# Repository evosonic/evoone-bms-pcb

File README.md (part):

# EvoOne BMS PCB (EVO2513 v0.6.0)

KiCad project for the EvoOne battery management board, EVO2513 revision 0.6.0.
Revision 0.6.0 is the 0.5.0 design (the boards in field test) with the W16
review changes below. The project, schematic and PCB files are named
`EVO2513`; the project libraries keep their `EVO2513-0_5_0` names.

The design was converted to KiCad from the Altium sources supplied by Lattech.
The raw import needed several fixes before the schematic and PCB agreed; see
[Fixes after import](#fixes-after-import).

## Board

| | |
|---|---|
| Outline | 110 × 69 mm |
| Layers | 8 copper (F.Cu, In1–In6.Cu, B.Cu) |
| Thickness | 1.598 mm finished (1.59 mm laminate + ENIG); stackup as the Altium fab drawing: three 0.25 mm cores, 2116 prepregs, 1 oz copper |
| Components | ~230 footprints |
| Tool | KiCad 10.0 |

## Schematic sheets

The schematic is hierarchical: the root sheet `EVO2513.kicad_sch` holds
one sheet symbol per sheet, and each sheet is its own file. Open it from
`EVO2513.kicad_pro`.

| Sheet | Function | Key parts |
|---|---|---|
| S01 External Connectors | Board connectors, mounting and test points | J1–J6, TP1–TP26 |
| S02 Input Protection | Over/under-voltage and reverse-voltage protection on the input | LTC4365, DMT4011LFG N-FETs |
| S03 BMS Input and Output Monitor | Input/output current sensing and power-path switching | LTC1960, DMP3018SFV P-FETs, 2512 shunts |
| S04 Charger Regulation | Charger switching stage | LTC1960, L1 4.7 µH |
| S05 Battery Management | Dual-battery selection and management | LTC1960 |
| S06 STEP-Up Step-Down Reg | Buck-boost output regulator | LM51772, L2 0.68 µH |
| S07 Load Switch and I-Sense | Output load switches and current-sense amplifiers | TPS22811 ×3, TLV9002 ×2 |
| S08 IO Expander | SPI I/O expander driving the rail enables and reading the faults | PCAL9714 |

The LTC1960 dual battery charger/selector is a single IC (U1) split across
sheets S03–S05.

Nets that cross sheets leave each sheet through a hierarchical label and a
pin on its sheet symbol, and the root sheet joins the pins with local
labels. There are no global labels; those nets are named from the root
(`/DCBMS`, `/POS1`, …). Labels between device sheets show the direction of
power or signal flow (e.g. DCFILTERED is an output of S02 and an input to
S03); links to the connector sheet, S01, stay passive. Labels used on only one sheet are local, and power
nets use power symbols.

## Connectors

| Ref | Part |
|---|---|
| J1 | Molex 1053101204, 2.5 mm pitch |
| J2 | Molex 1053101114, 14-way 2.5 mm pitch, vertical |
| J3 | Amphenol BergStak 10144517-043802LF, 40-pin 0.8 mm receptacle |
| J4 | Molex 1053102204, 2.5 mm pitch |
| J5, J6 | Molex 1053091102, 2-way 2.5 mm pitch |

The thermistor nets on J3 pins 24 and 28 are deliberately swapped from the
Altium design. The swap went in with `6ce5d68`, whose commit message doesn't
mention it. Firmware written for the earlier pinout must swap its BMSTEMP and
REGTEMP channels.

| J3 pin | Altium design | Now |
|---|---|---|
| 24 | BMSTEMP (TH1) | REGTEMP (TH2) |
| 28 | REGTEMP (TH2) | BMSTEMP (TH1) |

## Files

- `EVO2513.kicad_pro` — project
- `EVO2513.kicad_sch` — root schematic sheet; `S0x *.kicad_sch` — the
  eight sheets
- `EVO2513.kicad_pcb` — PCB layout
- `FIRMWARE_NOTES.md` — what the MCU firmware must know about this revision:
  SPI and expander set-up, the inverted DAQ enable, load-switch thresholds and
  current-monitor scaling
- `EVO2513-0_5_0-import-fps.pretty/` — project footprint library (footprints
  extracted by the Altium import), registered in `fp-lib-table`. Chip resistors
  and capacitors, the small diodes and the LEDs instead use KiCad's
  standard libraries (`Resistor_SMD`, `Capacitor_SMD`, `Diode_SMD`, `LED_SMD`,
  `Package_TO_SOT_SMD`, `Package_DFN_QFN`)
- `EVO2513-0_5_0-lattech.kicad_sym` — project symbol library (nickname
  `Lattech Systems`): the Lattech symbols used by the board, extracted from
  the schematics, plus the PCAL9714 added for the W16 changes. It is not the complete Lattech library, which was not supplied.
  Resistors and capacitors use KiCad's standard `Device:R`, `Device:C` and
  `Device:C_Polarized` symbols, with value, footprint and part number in the
  symbol fields, so a value change needs no new symbol
- `EVO2513-0_5_0-altium-import.kicad_sym` — the 4 power symbols created by the
  Altium import. Both symbol libraries are registered in `sym-lib-table`.

## Design changes (W16 review)

Part and value changes from the W16 schematic review. None changes a
connection or the board copper.

| Ref | Was | Now | Why |
|---|---|---|---|
| Q1, Q3 | DMT4011LFG 40 V | DMT6007LFGQ-7 60 V | Margin against D1's clamp voltage |
| D1 | 1.5SMB27CA | 1.0SMBJ26CA (Diotec) | Stand-off above the 24 V supply; 42.1 V clamp |
| L1 | 4.7 µH SRP1265A-4R7M | 10 µH SRP1265A-100M | LTC1960's 10 µH minimum |
| C10 | 100 nF 16 V | 100 nF 50 V CC0402KPX7R9BB104 | Sits on VPLUS at ~23 V |
| R54 | 1 kΩ | 768 Ω RC0402FR-07768RL | SBC load-switch current limit (R22, R53, R71 stay 1 kΩ) |
| C16 | 220 nF 50 V C0G 0805 | 220 nF 50 V X7R CC0805KFX7R9BB224 | No 220 nF C0G 0805 exists |
| C39 | 470 pF | 1 nF | SW2 snubber, boost-mode ringing |
| C3, C11, C12 | 35 V | 50 V | DCFILTERED / DCBMS at 26.3 V |
| C44, C45, C48–C50, C54 | 16 V | 50 V | +12 V and the switched outputs |
| R1 | 620K (description 619K) | 619K | Value and description now agree |
| C2 | 100 µF (part number `35SVPF82M`) | 82 µF `35SVPF82M` | Matches the ordered part |
| C46, C47, C51 | 4.7 nF 50 V X7R 0402 | 1.8 nF 50 V X7R 0402 `CC0402KRX7R9BB182` | TPS22811 DVDT caps (U6, U7, U9): shorter output ramp, as ordered for C47; the loads have little capacitance |
| R24–R27 | 10 Ω | 0 Ω | Pack comms pass straight through; protection moves to the MCU board |
| D9, D10 | DT1240V3-04LP fitted | DNP | Go with R24–R27: wrong clamp level for 3.3 V, and the protected MCU is on another board |
| R14 | 0.01 Ω | 0.012 Ω Yageo `PA2512FKE7W0R012E` | Adapter limit 8.33 A, below the 9.2 A supply, so charging throttles before the supply trips |
| R36 | 61.9K fitted | DNP | VIN-FB goes to ground through R37, as required when PCM is unused |
| R59, R61, R76 / R60, R62, R77 | 1M / 130K | **390K / 51K** | TPS22811 PGTH dividers: 10.38 V threshold, string current 23.5 µA at threshold to meet TI's 20× PGTH leakage rule, so pin leakage can't push it near the rail |
| R67, R68, R81 | 2.2K | **4.7K** | PG LED (LED2–LED4) resistors from +3V3MCU: about half the current, ≈0.25 mA each instead of ≈0.55 mA, which saves ≈0.9 mA on battery with all three rails up. 4.7K is already on the BOM (R10) |
| R90–R92, R101 | 1M | 1.07M | OVLO trip 14.0 V, so a tripped switch recovers on the 12.03 V rail; R101 shares the BOM line |
| U6 EN/UVLO | ENDAQ from P0_0, R49 100K pull-down | R108 **619K** / R49 **75K** UVLO divider, Q24 shutdown FET with R109 **1.07M** / R110 **390K** gate bias; net `nENDAQ`, active low | DAQ 11 V undervoltage lockout (W16 handoff §4.4) |
| R41, R45 | 2.2R 1% 1206, 1/4 W | 2.2R 1% **1210**, 1/2 W (any standard thick film) | Snubber resistors. R41 (SW1) dissipates 0.31 W at 24 V and 0.38 W at the 26.3 V OV trip, 75% of 1/2 W: fine up to about 90 °C local ambient. R45 (SW2) 0.167 W, 33%. Power is set by C·V²·f, not the load, so it is continuous at 1.157 MHz; power-save mode lowers it at light load. Same length as 1206; the pads are 0.45 mm wider each side |
| Q4, Q5, Q12–Q15 | DMP3018SFV, PowerDI3333-8 (Type UX), imported Altium land | **DMP3007SCG-13** (Diodes, V-DFN3333-8 Type B, 6.8 mΩ max at −10 V), `Diodes_PowerDI3333-8`, copied from KiCad's standard `Package_SON` library into the project library so it can carry the source-drain keepout | PowerPath/battery FET thermal margin (W16 handoff). KiCad has no Type B footprint; the PowerDI3333-8 one matches Diodes' Type B suggested land except 0.1 mm more toe on each pad row, and adds segmented paste on the drain. Its drain is one pad, 5, so the project symbol `DMP3007SCG V-DFN3333-8` numbers D pins 5–8 and EP_D all 5. VGSS ±25 V as before. Diodes' datasheet (DS38990 rev 3-2) is still marked Advance Information |
| Q18 | CSD17304Q3 | unchanged (kept) | The W16 handoff suggested a lower-RDS(on) 30 V part for the 1.83 W boost-mode loss. Kept: it works and 15 units are in field test. Its thermal margin depends on copper: 46 °C/W on 1 in² against 158 °C/W on a minimum pad, so give it the full copper area in layout |
| R16 | 0.005R 2512 (`CRE2512-FZ-R005E-3`) | **0.003R** Bourns `CRE2512-FZ-R003E-3` | The LTC1960 latching breaker (90–115 mV for 15 ms) moves from 18–23 A to 30–38 A. 12 V peak load is about 7.5 A SBC (90 W) + 2.5 A J3 + DAQ, over the handoff's ~11 A threshold, and QE29 packs at ~21 A would sit at 105 mV, inside the trip window. Dissipation at 21 A drops from 2.2 W to 1.3 W. R16 feeds only the breaker comparator (SCP/SCN) |
| R53, R71 | 1K | unchanged | DAQ and EXT current limits (6595/R = 6.6 A, up to 7.1 A) sit above J6/J5's single 6.5 A contact. Left at 1K: DAQ's final load isn't known (stand-in device today) and EXT is unused. A note on S07 says to raise them to 1.2K or more once the loads are known |
| D4 | Pins named as a series pair | Pins named for the fitted common-anode BAT54A | Drawing and wiring were already right |

Connection options on U5 (LM51772), as 0R 0402 links so either build can be
fitted (lower right of S06):
nRST stays on DCBMS in both BIAS builds.

| Pin | Fitted | DNP (alternative) |
|---|---|---|
| MODE (7) | R86 to GND: power-save mode (W16 review) | R87 back to VCC2: forced PWM, as built before |
| ILIMCOMP/ISET (16) | R116 13K and C55 100 pF to GND: average current limit and current monitor enabled | R103 to VCC2: current limit disabled, as built before |
| FB/SEL_intFB (14) | R117 to VCC2: internal feedback divider, output voltage set over I2C | R46 62K / R47 5.62K external divider, as built before |
| BIAS (40) | R89 to +12V (U5's own output): the LM51772 datasheet's standard configuration (§7.3.5). VSMART runs the VCC2 regulator from the lower of VIN and BIAS once both exceed the switch-over threshold, so on the 24 V supply it drops from 12 V instead of 24 V; at start-up or with +12V shorted it falls back to VIN | R88 to DCBMS, as built on the field units |

U5 is configured over I2C by default, not by its CFG resistors (parts right
of the MODE/BIAS links on S06):

| Ref | Part | Function in the I2C build (default) |
|---|---|---|
| R38 | 0R, CFG1 (ADDR/SLOPE, pin 9) to GND | Selects I2C at address 0x6A. 6.49K instead selects resistor configuration with slope compensation 1.0 |
| R104 | 0R, SDA/CFG3 (pin 5) to J3.34 `MCU_ENDAQ` | SDA to the MCU |
| R105 | 0R, SCL/CFG4 (pin 6) to J3.36 `MCU_ENEXT` | SCL to the MCU |
| R106, R107 | 10K to +3V3MCU | SDA and SCL pull-ups (pins rated to 5.8 V). 10K keeps edges slow for EMC and limits the bus to 100 kHz standard mode |
| R30, R29 | 5.1K and 1.87K to GND, **DNP** | CFG3/CFG4 for the resistor build; fitted, they would load the bus |

To return to the resistor build, remove R104–R107, change R38 to 6.49K and fit
R29 and R30. J3.34 and J3.36 are also the direct-enable fallback through R97
and R98 (S08), so R97 and R98 stay unfitted while the I2C build is fitted. The
MCU pins on J3.34/J3.36 must support I2C.

U5 starts from its register defaults, not the resistor
settings, so firmware must write them before raising REGEN. They are latched
for as long as DCBMS is up, since nRST is tied to DCBMS. Defaults that differ
from the resistor build:
- slope compensation is 0.875 (R38 selects 1.0)
- VCC1, DRSS, hiccup mode and the current-limit options come from registers
  instead of R30 and R29
- the internal DAC becomes the current-limit reference (`ILIM_THRESHOLD`);
  ILIMCOMP/ISET now has R116 13K and C55 100 pF to GND, so the average
  current limit is active: set `ILIM_THRESHOLD` to the intended limit
- R117 selects the internal feedback divider (R46/R47 DNP), so the +12V
  output voltage comes from U5's registers, not a resistor divider
- constant dead time (`EN_CONST_TDEAD`) defaults off; R30 (CFG3 setting 7)
  turns it on

Overvoltage lockout on the load switches U6, U7 and U9 (TPS22811, S07): a
1.07 MΩ 1% resistor (R90, R91, R92) from +12V to nEN/OVLO (pin 2), with the
existing 100K 1% pull-downs R51, R52 and R70. Each switch turns off above
14.0 V (13.40–14.69 V over the ±2% pin threshold, 1% resistors and ±0.1 µA pin
leakage) and turns back on below 12.75 V (12.23–13.41 V), so a tripped switch
always recovers on U5's 12.03 V output. (1 MΩ gave 13.2 V, recovering at
11.50–12.60 V, which might not.) To revert, leave R90–R92 unfitted.
The power-good dividers on PGTH are R59, R61 and R76 (390K) over R60, R62 and
R77 (51K): PG rises at 10.38 V (9.62–11.17 V worst case) and falls at 9.43 V
(8.71–10.22 V). They were 1M over 130K, but the ±1 µA PGTH leakage across 1M
could put the threshold at 11.84 V, within 0.2 V of the rail. TI sizes the
string for at least 20× the PGTH leakage (20 µA); 390K/51K carries 23.5 µA at
the threshold and 27 µA at 12 V, and only while the switch is on, because the
dividers hang off the switch outputs. 51K is already on the BOM.
Undervoltage lockout on the DAQ switch U6 only: R108 619K from +12V over R49
75K on EN/UVLO (pin 1) turns U6 on at 11.10 V (10.63–11.91 V, including
1% resistors, ±0.1 µA pin and 0.5 µA FET leakage) and off at 10.09 V
(9.69–10.89 V). TI asks for a pull-up of at least 350 kΩ on supplies above
5 V. 1M/120K would keep the 11.2 V point, but leakage across 1M puts the
worst-case turn-on at 12.24 V, above the rail; 619K and 75K are already on
the BOM and keep it under 12 V. The
TPS22811's fixed hysteresis makes the turn-off point about 9% below turn-on,
so 11 V has to be the turn-on point. Because the divider now holds EN/UVLO,
the enable goes through Q24 (BSS138) from EN/UVLO to GND, and the expander net
is `nENDAQ`, active low: high or floating (POR, expander in reset or
unpowered) turns Q24 on and puts U6 in shutdown; low releases EN/UVLO to the
divider. R109 1.07M / R110 390K bias the gate from +12V to 3.21 V (2.83 V at
10.6 V, 4.0 V worst case at the 14.7 V OVLO limit), so the channel stays off
when the MCU board is unpowered, and the gate stays under 5 V. The divider
draws 8.2 µA from +12V (it was 94 µA with 100K/27K), and both values are
shared with other BOM lines. The gate's source impedance is 286K, so P0_1 can
stay push-pull: driven high to 3.3 V it still holds Q24 on and sinks at most
2.4 µA, and the R97 fallback can drive it from a 3.3 V MCU pin. SBC and EXT have no
UVLO. A note on S07 marks the DAQ circuit as deliberate.

If the UVLO causes trouble, R115 (0R, DNP) bypasses it. Fit R115 and remove
Q24, R108 and R109: `nENDAQ` then drives EN/UVLO directly, as ENSBC and
ENEXT drive U7 and U9, so P0_1 (or the R97 fallback) becomes active high and
DAQ has no undervoltage lockout. R110 390K in parallel with R49 75K (62.9K) is
the pull-down that holds U6 off while the expander is in reset or unpowered.
Leaving R108 or R109 fitted with R115 would put a +12V divider on EN/UVLO, so
remove both.

Rail enables and faults through a PCAL9714 SPI I/O expander (U11, new sheet
S08). It shares CLOCK/MOSI/MISO with U1 (LTC1960) and has its own chip
select, nCSIO, on J3.32, the pin that was ENSBC. Address 40h (ADDR to GND);
INT has a pull-up but isn't routed off the board. Both supplies are
+3V3MCU. RESET is held low by R100 (100K) and pulled to +3V3MCU by Q23
(BSS138, the same FET as Q20-Q22) whenever +12V is up: R99 100K /
R101 1.07M put about 11 V on its gate. With the 12 V rail off the expander is
in reset with every port an input, and RESET can never rise above
+3V3MCU, so nothing back-powers the expander. The switch point depends on
Q23's gate threshold (roughly 3.5-4 V on +12V with a BSS138) and has no hysteresis, so
firmware should wait for +12V before configuring the expander.

Q20–Q23 are onsemi BSS138 (SOT-23) in place of the DMN65D8LFB-7
(DFN1006, 1.0 × 0.6 mm). Use the plain BSS138 or another part without a
gate protection zener: the gates sit on 100K pull-ups (R63, R65, R78) and
the R99/R101 divider, and ESD-protected parts such as the 2N7002K or
BSS138BK leak up to about 10 µA, which would pull the PG high level down
by about 1 V. BSS138: IGSS 100 nA, IDSS 0.5 µA, VGS(th) 0.8–1.5 V.

| Port | Net | Function |
|---|---|---|
| P0_0 (out) | ENSBC | U7 enable |
| P0_1 (out) | nENDAQ | U6 enable through Q24, **active low** |
| P0_2 (out) | ENEXT | U9 enable |
| P0_4–P0_6 (in) | PGDAQ, PGSBC, PGEXT | U6, U7, U9 power good (also still drive the LEDs) |
| P0_7 (in) | nFLT | U5 nFLT/nINT, which was unconnected |
| P0_3, P1_0–P1_5 | — | spare, not connected |

REGEN (U5 enable, J3.12) stays separate: it is still driven straight from
J3 and doesn't pass through the expander.

J3 pins 34 and 36 are now `MCU_ENDAQ` and `MCU_ENEXT`. Each reaches its
enable only through a DNP 0R link (R97, R98), and J3.32
`nCSIO` has R95 (fitted) to the expander CS and R96 (DNP) to ENSBC. To go
back to driving an enable straight from J3, fit its link and leave that
expander port an input. The expander powers up with every port an input
and pulls off, so the pull-downs (R50, R69) and Q24's gate bias keep the
rails off until firmware sets P0_0–P0_2 as outputs. R97 now lands on
`nENDAQ`, so an MCU driving DAQ directly must drive it low to enable. The MCU firmware must change for this:
the three load-switch enables move from GPIO to SPI, and nCSIO must idle high (R93
pulls it up).

These parts aren't on the board yet: run Update PCB from Schematic, then
place and route R86–R110, Q23, Q24, U11, C58 and C59, and re-place Q20–Q22
(now SOT-23). The ENDAQ, ENSBC and ENEXT
tracks from J3 need cutting at the new links.

## BOM consolidation

Parts with the same value in different packages or ratings now share one BOM
line. Each change keeps or raises the voltage rating and tolerance.
All resistors are 1%: the OVLO dividers moved from 1M/102K 0.1% to
1.07M/100K 1% (see the overvoltage lockout above), and R101 is 1.07M to share
their BOM line.

| Refs | Was | Now |
|---|---|---|
| C8, C9 | 1 µF 50 V X5R 0402 | 1 µF 50 V X5R **0603**, as C23, C44, C45, C48–C50, C54 |
| C7, C52, C53, C58, C59 | 100 nF 16 V X7R 0402 | 100 nF **50 V** X7R 0402 `CC0402KPX7R9BB104`, as C10 |
| C37, C38 | 100 nF 16 V X7R 0603 | the same, **0402** (U5 bootstrap caps, ~5 V) |
| C17, C18, C20, C21, C34 | 100 nF 50 V X7R 0402, no part number | `CC0402KPX7R9BB104` |
| C11–C14, C24–C26 | 10 µF 25 V/50 V 1206 | 10 µF 50 V X7R **1210** Taiyo Yuden `UMK325AB7106KMHP`, as C27 (1210 is easier to source) |
| C27 | 10 µF 50 V X5R 1210 | the same part, X7R |
| C16 | 220 nF 50 V X7R 0805 | the same, **0603** Yageo `AC0603KRX7R9BB224`, as C22 (charger bootstrap cap) |
| C22 | 220 nF 50 V 0603, material field X5R | X7R, as its description already said |
| R43, R44 | 10R 1% 0603 | 10R 1% **0402**, as R4, R5, R24–R27 (U5 current-sense filter, no power) |

Five U5 (LM51772) changes found during the review:

| Ref | Was | Now | Why |
|---|---|---|---|
| C30 → **R102** | 22 µF 6.3 V 0603 on VCC1 | 10K 1% 0402 to GND, as R7 | VCC1 is disabled (R30 5.1K on CFG3); the datasheet says tie a disabled VCC1 to GND through a resistor, not leave it floating |
| C32 | 22 µF 6.3 V X5R 0603 on VCC2 | 22 µF **16 V** X5R **0805** Murata `GRM219R61C226ME15L` | VCC2 needs 6 µF minimum; the 0603 keeps only about 5–7 µF at 5 V |
| R29 | 1.9K | **1.87K** | CFG4 setting #3 accepts 1.814–1.926 kΩ (1.87K typical); 1.9K isn't a 1% value, and 1.91K can reach 1.929 kΩ |
| **C61** (new) | — | 100 nF 50 V X7R 0402 `CC0402KPX7R9BB104` (as C34), BIAS (pin 40) to GND, between R88 and R89 | BIAS had no local decoupling; TI's WEBENCH design puts 100 nF (Cbias) on it. The +12V caps are about 4.6 mm away through R89 |
| R46 (FB top) | on the power-stage side of R48 | on **+12V**, teed into the ISNSN Kelvin trace from R48's load-side pad | +12V is regulated after the 5 mΩ shunt, so it no longer sags by R48's drop (about 55 mV at 11 A). Matches the datasheet's Figure 9-1 and §9.9.1.3 (route the top feedback resistor to the output sense point). VOUT (pin 18) stays on the power stage. Since superseded: R46/R47 are DNP and R117 selects the internal feedback divider |

Run Update PCB from Schematic to swap the footprints. Parts that grow overlap
their neighbours' courtyards and need moving: the 0603s for C8 and C9 by up
to 0.9 mm (C8 against R8, C9 against R15 and C10),
the 1210s by about 0.15 mm (C11/C12/C27, C24/C26, C25 against C23), and C32
by 0.3 mm against C38 (before C38 shrinks to 0402) and 0.1 mm against TH2.

### Manufacturer part numbers

`MANUFACTURER` and `MANUFACTURER_PN` are filled on every fitted part, in the
schematic and on the board. Parts unchanged since 0.5.0 carry the exact part
numbers bought for the 0.5.0 backup build (DigiKey list for 20 boards, plus a
Mouser order for LM51772RHAR, DMT6007LFGQ-7 and DMT4011LFG-7). Parts that
changed reuse a bought part where value, package and rating match (for
example the 390K/51K PGTH dividers take the R9 51K part). Parts with no earlier
order keep the schematic's part number, or take a Yageo RC/CC-series part:
`RC0402JR-070RL` (0R), `RC0402FR-07390KL`, `RC0402FR-071M07L`,
`RC0402FR-071K87L`, `RC1210FR-072R2L`, `CC0805KPX7R9BB102`,
`CC0603KRX7R9BB104`. Resistors are standardised on Yageo (R31
`RC0402FR-1340K2L`, R111–R114 `RC0603FR-073RL`), except the current-sense
shunts R16, R19, R42 and R48. D6–D8 are `B340A-13-F`. M1–M6 are Würth
`78614150960`.

Five lines use parts held in stock from the 0.5.0 orders, with the earlier
schematic part kept in the NOTE field as `Alternate: <manufacturer> <part number>`:

| Ref | Fitted part | Alternate (NOTE) |
|---|---|---|
| C6 | Yageo `CC0402KRX7R9BB182` 1.8 nF 50 V X7R, as C46, C47, C51 | KEMET `C0402C182K4RACTU` |
| C8, C9, C23, C44, C45, C48–C50, C54 | Samsung `CL10A105KB8NNNC` 1 µF 50 V X5R 0603 | Murata `GRT188R61H105KE13D` (AEC-Q200) |
| C15 | KEMET `C0805C475K8PACTU` 4.7 µF 10 V X5R 0805 | Murata `GRM219R61A475KE34J` |
| D2 | MCC `MBR0540-TP` | Panjit `SS0540_R1_00001` |
| L2 | Würth `744393580068` 0.68 µH, on the XAL8080 footprint | Coilcraft `XAL8080-681MEB` |

Four lines carry the part numbers actually bought (DigiKey order 102349469 for
the 15-board build, and the 0.5.0 Mouser order for Q6–Q11), with the earlier
part kept in the NOTE field the same way:

| Ref | Fitted part | Alternate (NOTE) |
|---|---|---|
| Q1, Q3 | Diodes `DMT6007LFG-7` (commercial grade) | Diodes `DMT6007LFGQ-7` (AEC-Q101) |
| Q6–Q11 | Diodes `DMT4011LFG-7` (7″ reel) | Diodes `DMT4011LFG-13` (13″ reel) |
| R10, R67, R68, R81 | Yageo `RC0402FR-134K7L` (13″ reel) | Yageo `RC0402FR-074K7L` (7″ reel) |
| R41, R45 | Yageo `AC1210FR-072R2L` (AEC-Q200) | Yageo `RC1210FR-072R2L` |

## Fixes after import

Each fix is a separate commit on top of the initial import.

| Problem in the raw import | Fix |
|---|---|
| Every symbol's Value field was `${ALTIUM_VALUE}`, resolved through a per-symbol field | Copied the real value into Value (209 symbols); the 26 test points, which had no value, are `POGO-1` |
| 12 Footprint fields differed from the placed footprint only in letter case, so library lookup failed | Fields now name the exact footprint used on the PCB (J2, J5, J6, M2–M6, FL1, D9, D10, L2) |
| An imported `FOOTPRINT` field holding the bare package name (`0402`, `SMA`, …) overrode the real Footprint field, since KiCad matches field names case-insensitively | Renamed to `ALTIUM_FOOTPRINT` on all 237 symbols |
| Altium net labels became KiCad local labels, which don't connect across sheets, splitting 35 nets | Converted the 78 labels for those nets to global labels |
| 44 embedded library symbols drew Altium special strings `=Value` and `=FootPrint` as literal text | `=Value` replaced with `${VALUE}`; `=FootPrint` replaced by showing each part's own `ALTIUM_FOOTPRINT` field in the same place, so parts show their part number and package as in Altium |
| All 99 power symbols were unannotated (`#PWR?`) | Annotated `#PWR1`–`#PWR99` |
| The "Lattech Systems" symbol library wasn't available, so symbols existed only as copies embedded in the schematics, some in several slightly different versions | Exported the symbols to project libraries under their original library names, and made every schematic use one definition per symbol |
| Chip resistor and capacitor footprints had poor pads (0402s used 0.635 mm circular pads) and caused tombstoning | Replaced all 139 with KiCad standard IPC-7351 nominal footprints (`Resistor_SMD`, `Capacitor_SMD`) in place: same position, rotation and nets, zones refilled |
| Diodes and LEDs used imported Altium lands where KiCad has a standard IPC-7351 footprint; the LED land carried A/C silk text below the minimum thickness (8 DRC warnings) | Swapped to KiCad standard footprints in place (same position, side and nets; pad centres within 0.33 mm): D1 `Diode_SMD:D_SMB`, D6–D8 `Diode_SMD:D_SMA`, D4 `Package_TO_SOT_SMD:SOT-23` (as Q20–Q24), D9/D10 `Package_DFN_QFN:Diodes_UDFN-10_1x2.5mm_P0.5mm` (identical pads), LED1–LED4 `LED_SMD:LED_0603_1608Metric`, turned 180° because its pad 1 (cathode) is on the other side. The SMA/SMB pads are 0.6–0.7 mm longer towards the body. The power FETs keep their imported lands: they match the manufacturers' suggested layouts, KiCad's equivalents number the whole drain as one pad, and Q18's land is proven on the field units. The five unused imported footprints are removed from the project library |
| PCB footprints were linked to the imported symbols by mismatched internal IDs, and nets used Altium names | Ran Update PCB from Schematic: no errors, placement and copper unchanged, all 147 nets match the schematic |
| KiCad design rules were defaults (0.2 mm clearance and track, 0.3 mm min hole), not the Altium rules | Set to the rules in the Altium `.PcbDoc`: 0.15 mm clearance, track and annular ring, 0.15 mm min hole, 0.3 mm hole-to-hole, and `EVO2513.kicad_dru` for the 0.3 mm pad-to-pad rule on test points TP1–TP26 |
| The import turned 347 Altium copper regions into board graphic polygons (`gr_poly`) on B.Cu and In1–In6: a 1.2 × 1.8 mm octagon over each six-via block, on every layer. As drawings they bypass zone clearance and fill rules, and on the GND layers most were net islands in the GND pour, including the charger switch node (Net-(D2-C)) | Removed all of them. None carried current: each only joined its own vias, which every same-net pour already connects solid, and DRC finds 0 unconnected without them. GND gains about 26 mm² on In1, 21 mm² on In3 and In5, 18 mm² on In6 and 27 mm² on B.Cu |
| FL1's ground land had no pad number, so its 38 GND vias showed as shorts | Numbered pad 4 (GND) on the board and in the project footprint library |
| The two mounting holes and the logo existed only on the board, with no schematic symbols | H1 and H2 (`Mechanical:MountingHole_Pad`, pin 1 to GND, project footprint `MountingHole_3.2mm_Pad_7.4mm`) and LOGO01 (`EVOSONIC_LOGO`, a pinless symbol in the Lattech library) are on the root sheet, excluded from BOM and position files. Update PCB from Schematic no longer deletes them |
| 14 zero-length track segments | Removed |
| FL1's courtyard had a centre cross drawn on F.CrtYd, so KiCad saw an open (malformed) courtyard | Moved the cross to F.Fab on the board and in the project footprint library |
| Two vias sat in 0402 pads (R13 pad 2, R54 pad 2), connected on F.Cu only, and could wick solder | Removed |
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
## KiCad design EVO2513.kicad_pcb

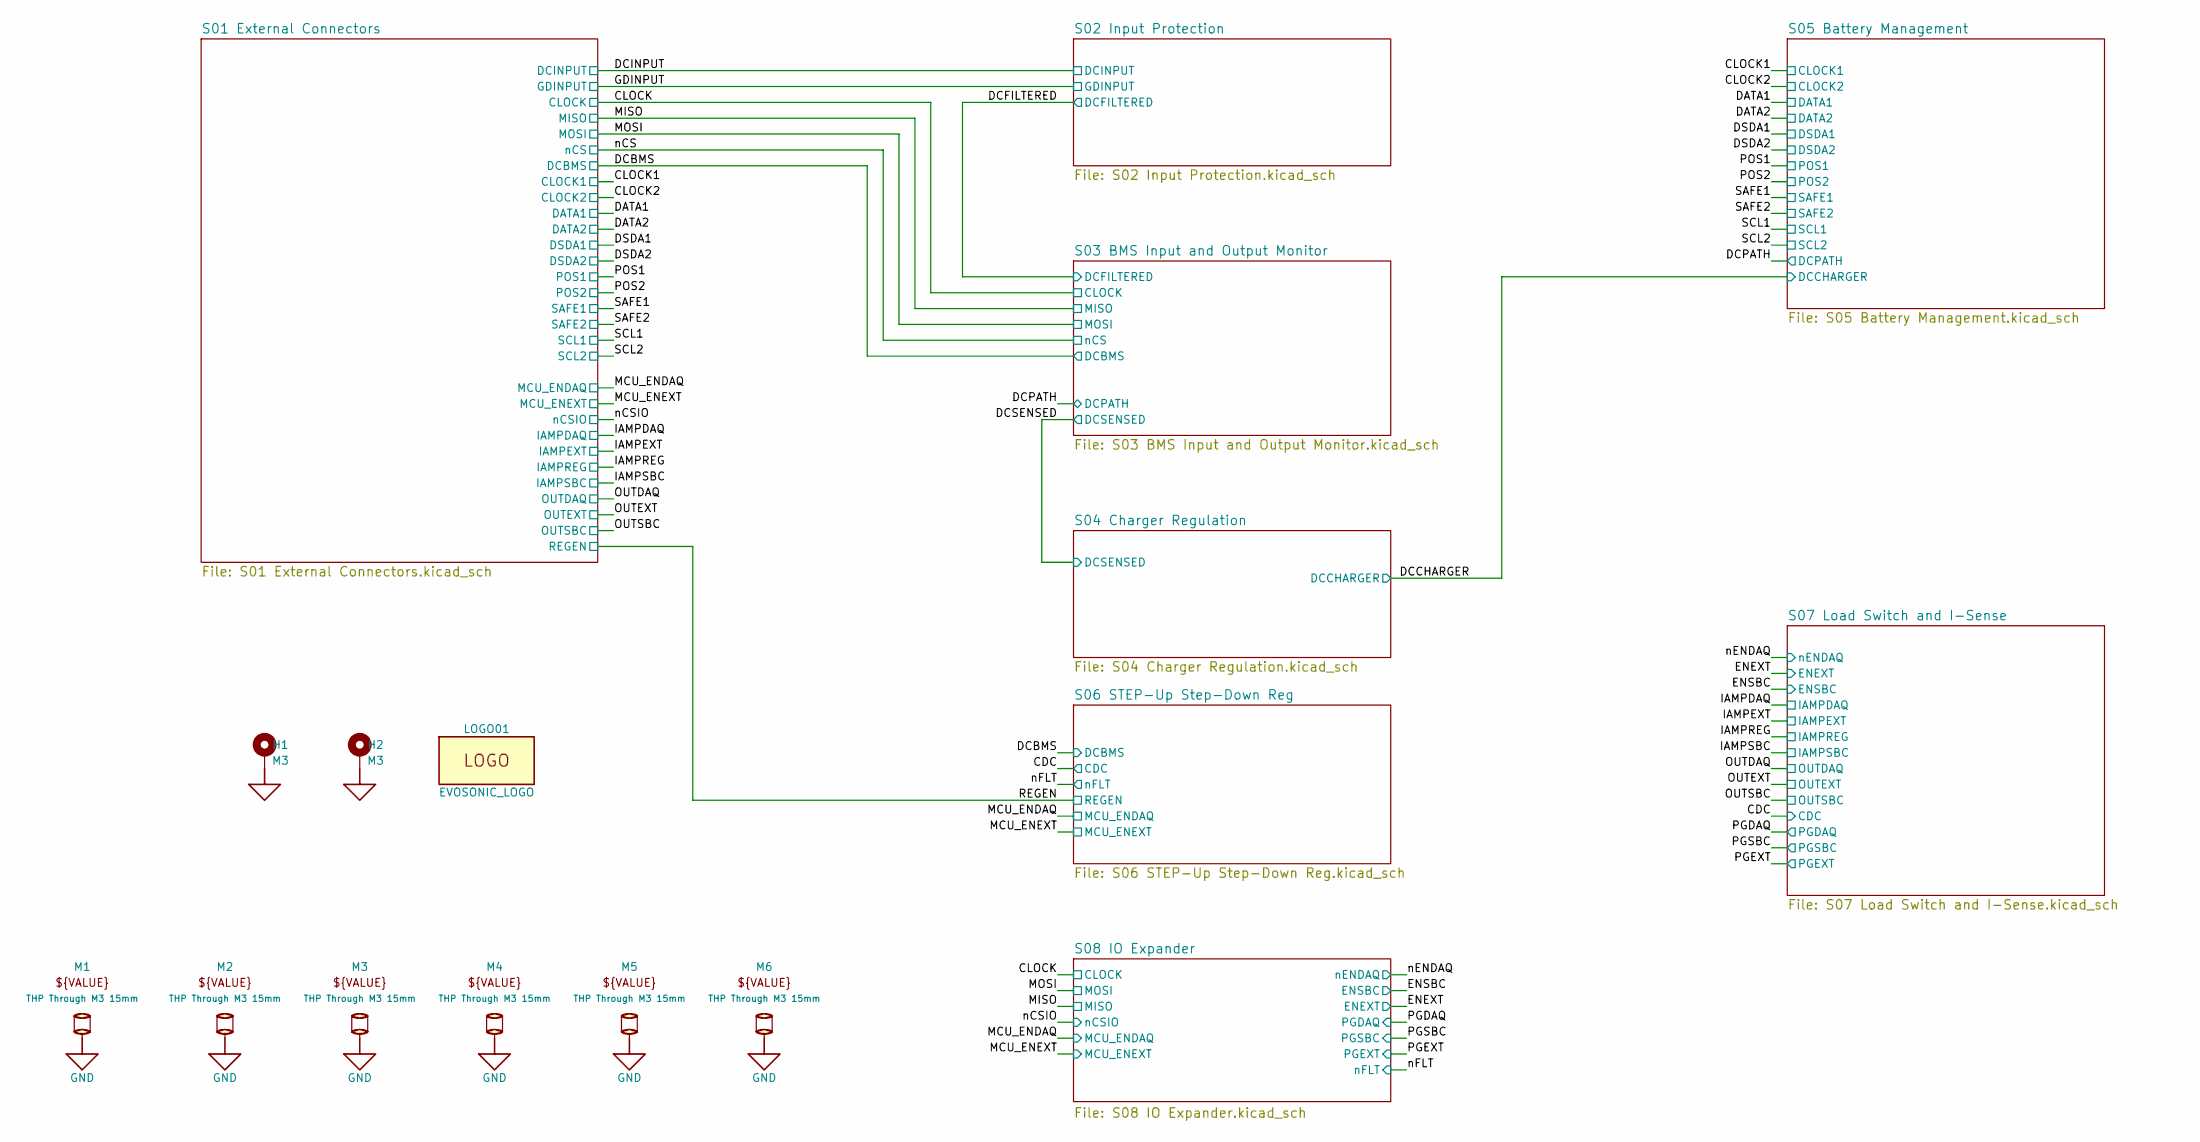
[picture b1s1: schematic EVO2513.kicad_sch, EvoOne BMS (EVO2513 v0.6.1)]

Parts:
H1, H2: M3; MountingHole_3.2mm_Pad_7.4mm
LOGO01: EVOSONIC_LOGO; EVOSONIC_DNA_LOGO_390X600_MASK
M1, M2, M3, M4, M5, M6: 78614150960; MECH SPACER WURTH 78614150960 THROUGH M3; MANUFACTURER_PN 78614150960

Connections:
GND: H1.1 (1_1), H2.1 (1_1), M1.1 (1_1), M2.1 (1_1), M3.1 (1_1), M4.1 (1_1), M5.1 (1_1), M6.1 (1_1); also elsewhere on the board

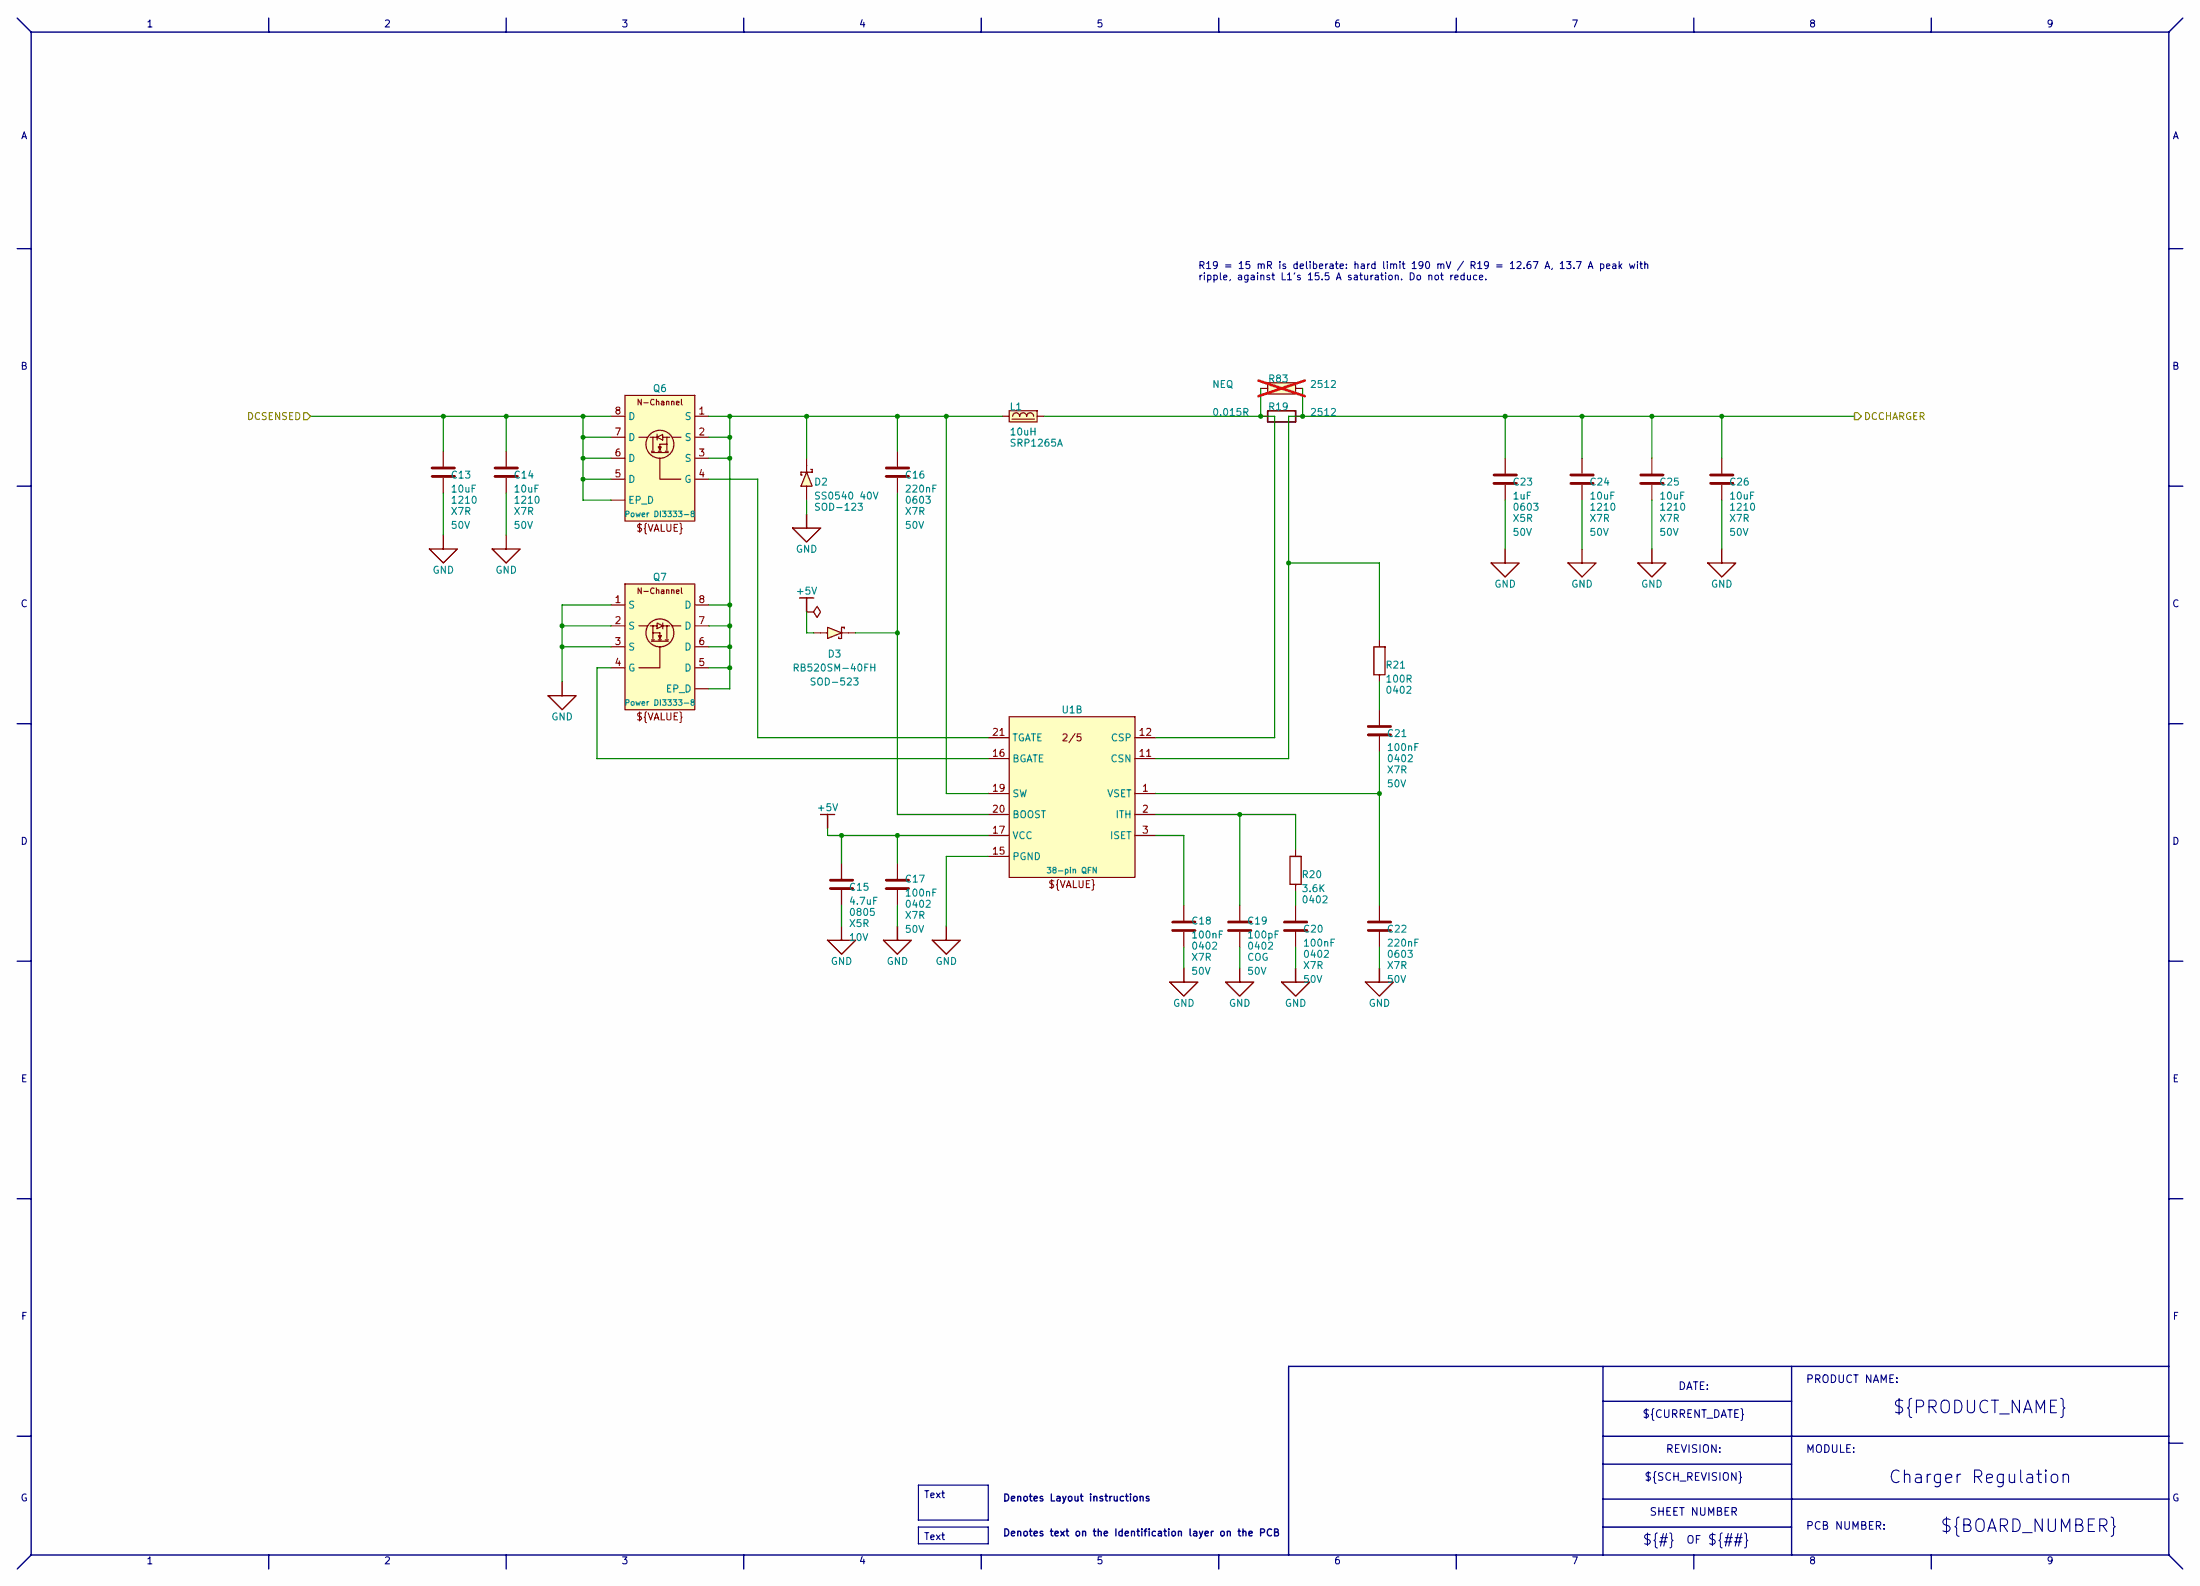
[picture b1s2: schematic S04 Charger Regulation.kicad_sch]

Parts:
C13, C14, C24, C25, C26: 10uF; C_1210_3225Metric; VOLTAGE 50V; MANUFACTURER_PN UMK325AB7106KMHP
C15: 4.7uF; C_0805_2012Metric; VOLTAGE 10V; MANUFACTURER_PN C0805C475K8PACTU
C16, C22: 220nF; C_0603_1608Metric; VOLTAGE 50V; MANUFACTURER_PN AC0603KRX7R9BB224
C17, C18, C20, C21: 100nF; C_0402_1005Metric; VOLTAGE 50V; MANUFACTURER_PN CC0402KPX7R9BB104
C19: 100pF; C_0402_1005Metric; VOLTAGE 50V; MANUFACTURER_PN CC0402JRNPO9BN101
C23: 1uF; C_0603_1608Metric; VOLTAGE 50V; MANUFACTURER_PN CL10A105KB8NNNC
D2: MBR0540 40V; D_SOD-123; MANUFACTURER_PN MBR0540-TP
D3: RB520SM-40FH; D_SOD-523; MANUFACTURER_PN RB520SM-40FHT2R
L1: 10uH; IND Bourns SRRP1265A; MANUFACTURER_PN SRP1265A-100M
Q6, Q7: DMT4011LFG; Power DI3333-8 B3.3 x 3.3 P0.65 Tab 8-Pin; MANUFACTURER_PN DMT4011LFG-7
R19: 0.015R; R_2512_6332Metric; MANUFACTURER_PN CRA2512-FZ-R015ELF
R20: 3.6K; R_0402_1005Metric; MANUFACTURER_PN RC0402FR-073K6L
R21: 100R; R_0402_1005Metric; MANUFACTURER_PN RC0402FR-07100RL
R83: NEQ; R_2512_6332Metric; MANUFACTURER_PN Res 2512; not fitted
U1: LTC1960; QFN B5x7 P0-5 38-Pin EP; MANUFACTURER_PN LTC1960CUHF#PBF

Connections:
+5V: C15.2, C17.2, D3.2 (A), U1.17 (VCC); also elsewhere on the board
/DCCHARGER: C23.2, C24.2, C25.2, C26.2, R19.2, R21.2, R83.2, U1.11 (CSN); also elsewhere on the board
/DCSENSED: C13.2, C14.2, Q6.5 (D), Q6.6 (D), Q6.7 (D), Q6.8 (D), Q6.9 (EP_D); also elsewhere on the board
GND: C13.1, C14.1, C15.1, C17.1, C18.1, C19.1, C20.1, C22.1, C23.1, C24.1, C25.1, C26.1, D2.2 (A), Q7.1 (S), Q7.2 (S), Q7.3 (S), U1.15 (PGND); also elsewhere on the board
unnamed: C20.2, R20.1
unnamed: C21.2, R21.1
unnamed: C16.2, D2.1 (C), L1.1, Q6.1 (S), Q6.2 (S), Q6.3 (S), Q7.5 (D), Q7.6 (D), Q7.7 (D), Q7.8 (D), Q7.9 (EP_D), U1.19 (SW)
unnamed: C16.1, D3.1 (C), U1.20 (BOOST)
unnamed: Q6.4 (G), U1.21 (TGATE)
unnamed: Q7.4 (G), U1.16 (BGATE)
unnamed: L1.2, R19.1, R83.1, U1.12 (CSP)
unnamed: C18.2, U1.3 (ISET)
unnamed: C19.2, R20.2, U1.2 (ITH)
unnamed: C21.1, C22.2, U1.1 (VSET)

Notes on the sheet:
${##}
Charger Regulation
REVISION:
${BOARD_NUMBER}
${#}
R19 = 15 mR is deliberate: hard limit 190 mV / R19 = 12.67 A, 13.7 A peak with ripple, against L1's 15.5 A saturation. Do not reduce.
${PRODUCT_NAME}
Denotes Layout instructions
PCB NUMBER:
${CURRENT_DATE}
PRODUCT NAME:
${SCH_REVISION}
Denotes text on the Identification layer on the PCB
MODULE:
SHEET NUMBER
DATE:
Text

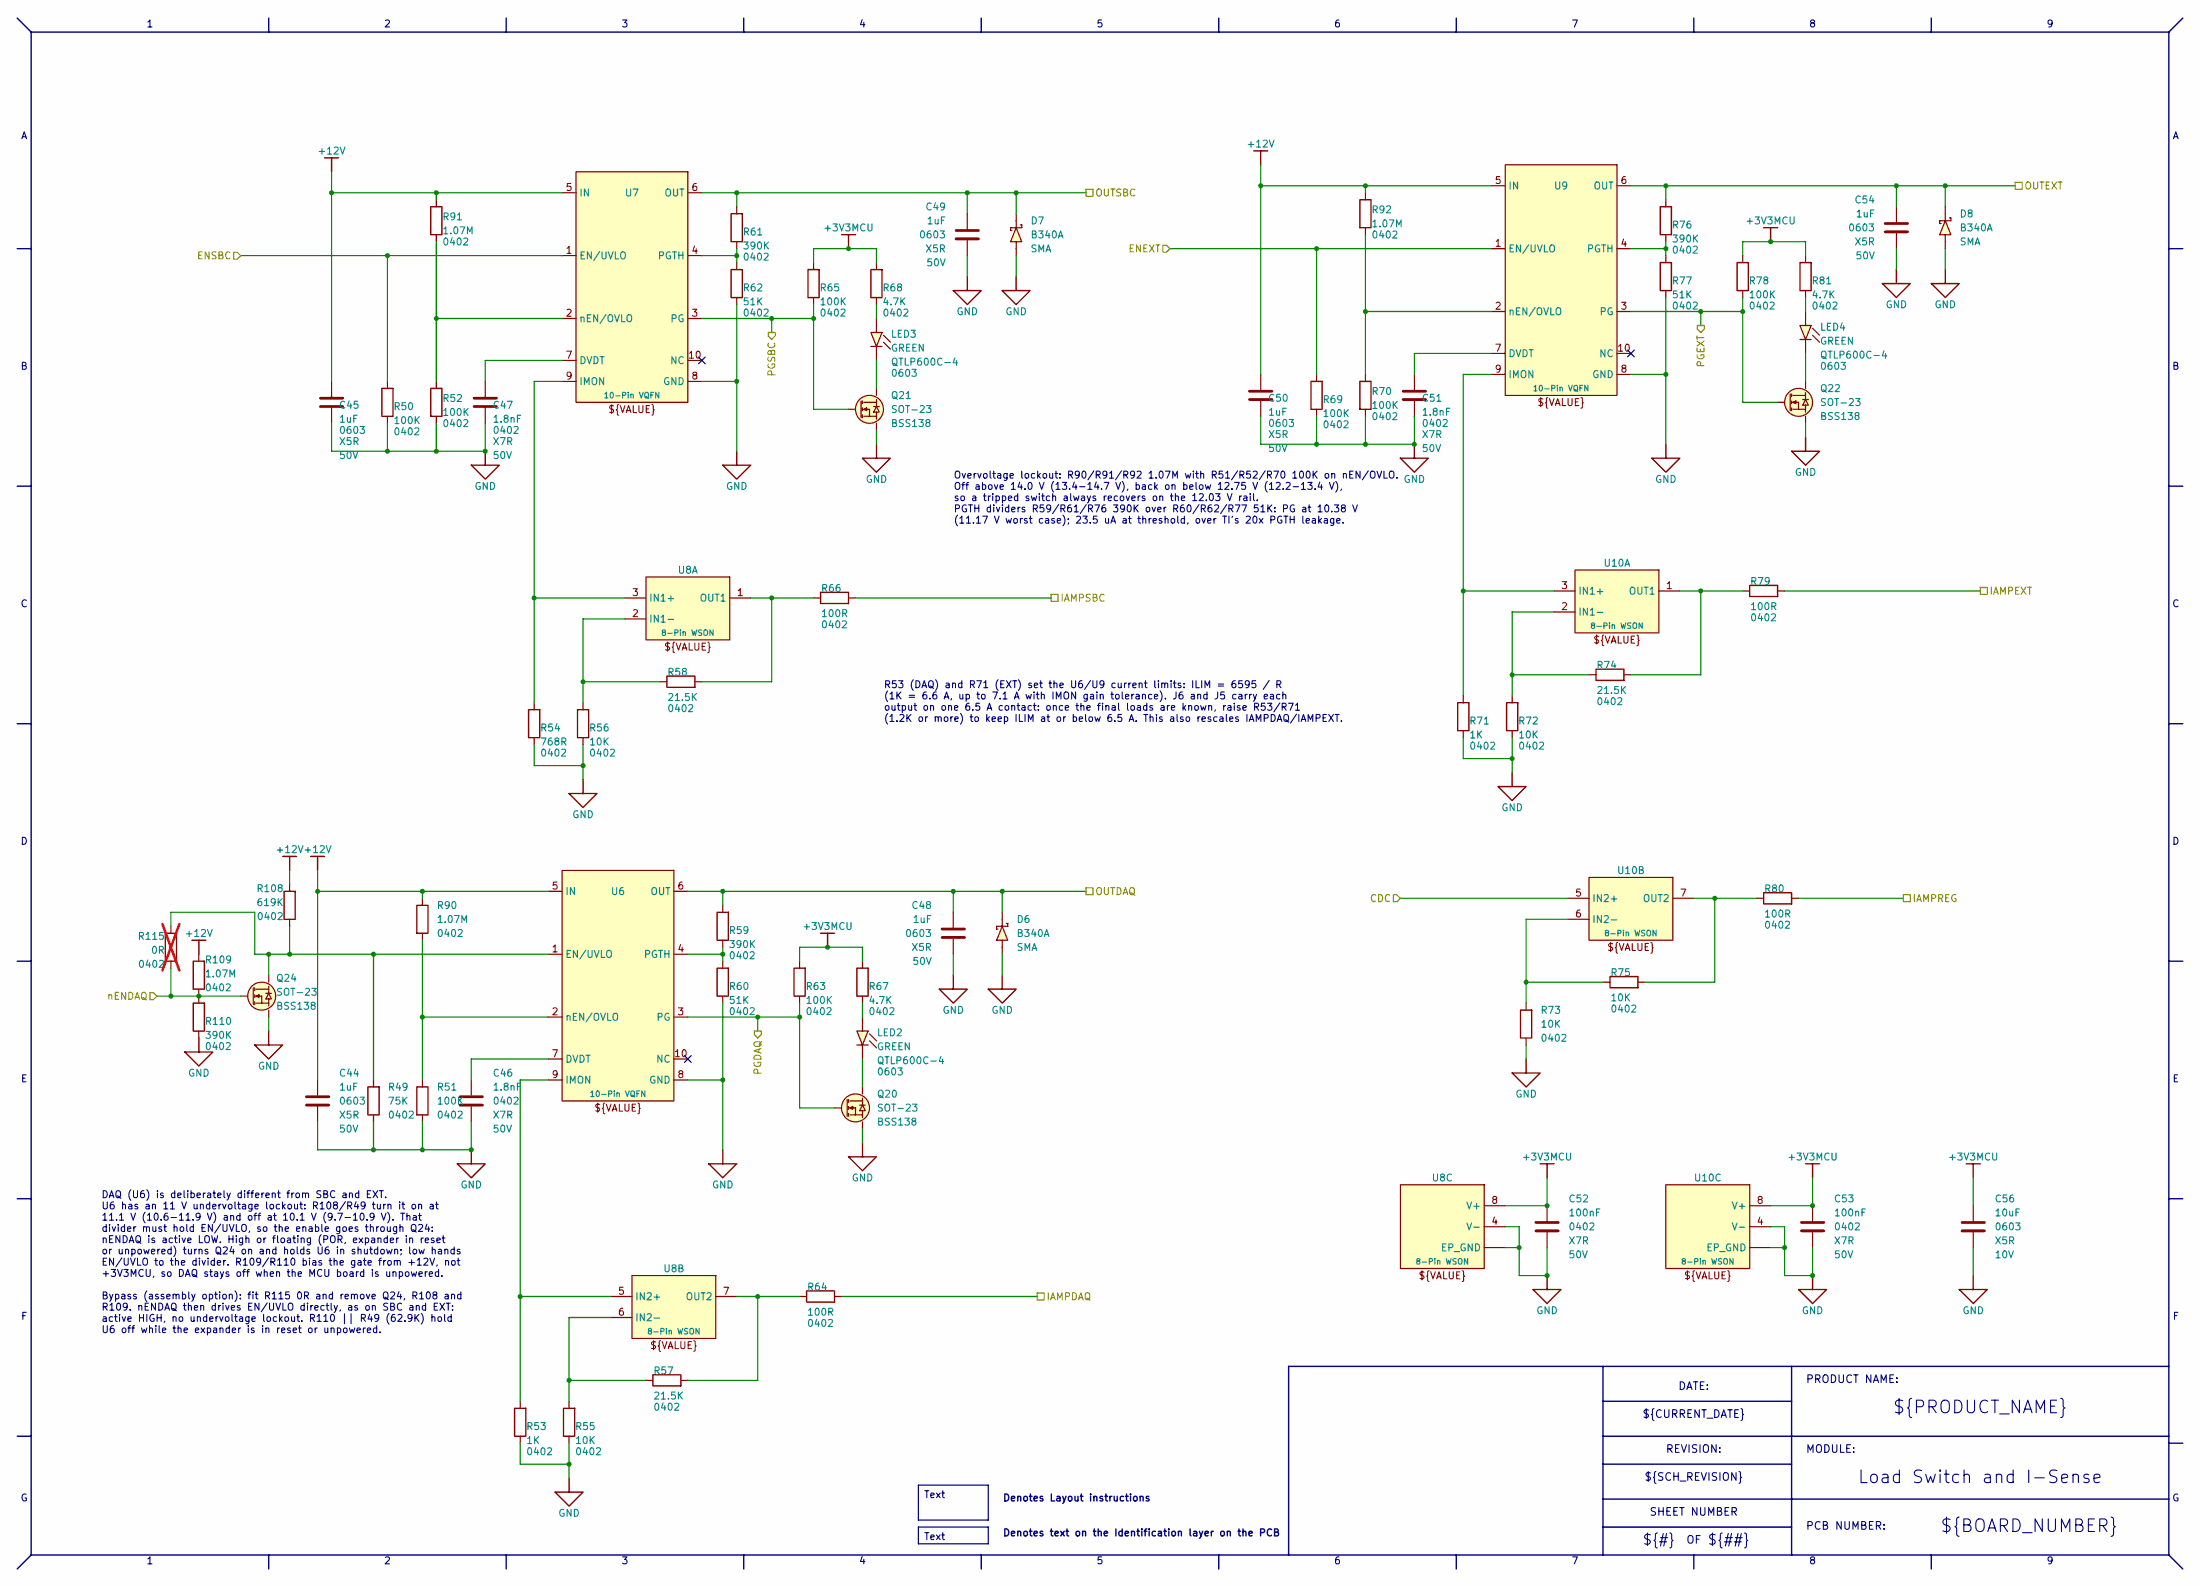
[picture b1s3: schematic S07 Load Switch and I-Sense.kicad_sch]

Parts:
C44, C45, C48, C49, C50, C54: 1uF; C_0603_1608Metric; VOLTAGE 50V; MANUFACTURER_PN CL10A105KB8NNNC
C46, C47, C51: 1.8nF; C_0402_1005Metric; VOLTAGE 50V; MANUFACTURER_PN CC0402KRX7R9BB182
C52, C53: 100nF; C_0402_1005Metric; VOLTAGE 50V; MANUFACTURER_PN CC0402KPX7R9BB104
C56: 10uF; C_0603_1608Metric; VOLTAGE 10V; MANUFACTURER_PN CC0603KRX5R6BB106
D6, D7, D8: B340A; D_SMA; MANUFACTURER_PN B340A-13-F
LED2, LED3, LED4: QTLP600C-4; LED_0603_1608Metric; MANUFACTURER_PN QTLP600C4TR
Q20, Q21, Q22, Q24: BSS138; SOT-23; MANUFACTURER_PN BSS138
R49: 75K; R_0402_1005Metric; MANUFACTURER_PN RC0402FR-0775KL
R50, R51, R52, R63, R65, R69, R70, R78: 100K; R_0402_1005Metric; MANUFACTURER_PN RC0402FR-07100KL
R53, R71: 1K; R_0402_1005Metric; MANUFACTURER_PN RC0402FR-071KL
R54: 768R; R_0402_1005Metric; MANUFACTURER_PN RC0402FR-07768RL
R55, R56, R72, R73, R75: 10K; R_0402_1005Metric; MANUFACTURER_PN RC0402FR-0710KL
R57, R58, R74: 21.5K; R_0402_1005Metric; MANUFACTURER_PN RC0402FR-0721K5L
R59, R61, R76, R110: 390K; R_0402_1005Metric; MANUFACTURER_PN RC0402FR-07390KL
R60, R62, R77: 51K; R_0402_1005Metric; MANUFACTURER_PN RC0402FR-0751KL
R64, R66, R79, R80: 100R; R_0402_1005Metric; MANUFACTURER_PN RC0402FR-07100RL
R67, R68, R81: 4.7K; R_0402_1005Metric; MANUFACTURER_PN RC0402FR-134K7L
R90, R91, R92, R109: 1.07M; R_0402_1005Metric; MANUFACTURER_PN RC0402FR-071M07L
R108: 619K; R_0402_1005Metric; MANUFACTURER_PN RC0402FR-07619KL
R115: 0R; R_0402_1005Metric; MANUFACTURER_PN RC0402JR-070RL; not fitted
U6, U7, U9: TPS22811; VQFN-HR B2.0x2.0x1.0 10-Pin TI LM73100RPW; MANUFACTURER_PN TPS22811LRPWR
U8, U10: TLV9002IDSG; WSON B2x2 P0-5 8-Pin EP; MANUFACTURER_PN TLV9002IDSGR

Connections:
+3V3MCU: C52.2, C53.2, C56.2, R63.2, R65.2, R67.2, R68.2, R78.2, R81.2, U8.8 (V+), U10.8 (V+); also elsewhere on the board
+12V: C44.2, C45.2, C50.2, R90.1, R91.1, R92.1, R108.2, R109.2, U6.5 (IN), U7.5 (IN), U9.5 (IN); also elsewhere on the board
/CDC: U10.5 (IN2+); also elsewhere on the board
/ENEXT: R69.2, U9.1 (EN/UVLO); also elsewhere on the board
/ENSBC: R50.2, U7.1 (EN/UVLO); also elsewhere on the board
/IAMPDAQ: R64.2; also elsewhere on the board
/IAMPEXT: R79.2; also elsewhere on the board
/IAMPREG: R80.2; also elsewhere on the board
/IAMPSBC: R66.2; also elsewhere on the board
/OUTDAQ: C48.2, D6.1 (C), R59.2, U6.6 (OUT); also elsewhere on the board
/OUTEXT: C54.2, D8.1 (C), R76.2, U9.6 (OUT); also elsewhere on the board
/OUTSBC: C49.2, D7.1 (C), R61.2, U7.6 (OUT); also elsewhere on the board
/PGDAQ: Q20.1 (G), R63.1, U6.3 (PG); also elsewhere on the board
/PGEXT: Q22.1 (G), R78.1, U9.3 (PG); also elsewhere on the board
/PGSBC: Q21.1 (G), R65.1, U7.3 (PG); also elsewhere on the board
/nENDAQ: Q24.1 (G), R109.1, R110.2, R115.2; also elsewhere on the board
GND: C44.1, C45.1, C46.1, C47.1, C48.1, C49.1, C50.1, C51.1, C52.1, C53.1, C54.1, C56.1, D6.2 (A), D7.2 (A), D8.2 (A), Q20.2 (S), Q21.2 (S), Q22.2 (S), Q24.2 (S), R49.1, R50.1, R51.2, R52.2, R53.1, R54.1, R55.1, R56.1, R60.1, R62.1, R69.1, R70.2, R71.1, R72.1, R73.1, R77.1, R110.1, U6.8 (GND), U7.8 (GND), U8.4 (V-), U8.9 (EP_GND), U9.8 (GND), U10.4 (V-), U10.9 (EP_GND); also elsewhere on the board
unnamed: LED2.2 (A), R67.1
unnamed: LED2.1 (C), Q20.3 (D)
unnamed: LED3.2 (A), R68.1
unnamed: LED3.1 (C), Q21.3 (D)
unnamed: LED4.2 (A), R81.1
unnamed: LED4.1 (C), Q22.3 (D)
unnamed: Q24.3 (D), R49.2, R108.1, R115.1, U6.1 (EN/UVLO)
unnamed: C46.2, U6.7 (DVDT)
unnamed: R53.2, U6.9 (IMON), U8.5 (IN2+)
unnamed: R59.1, R60.2, U6.4 (PGTH)
unnamed: R51.1, R90.2, U6.2 (nEN/OVLO)
unnamed: C47.2, U7.7 (DVDT)
unnamed: R54.2, U7.9 (IMON), U8.3 (IN1+)
unnamed: R61.1, R62.2, U7.4 (PGTH)
unnamed: R52.1, R91.2, U7.2 (nEN/OVLO)
unnamed: R56.2, R58.1, U8.2 (IN1-)
unnamed: R58.2, R66.1, U8.1 (OUT1)
unnamed: R55.2, R57.1, U8.6 (IN2-)
unnamed: R57.2, R64.1, U8.7 (OUT2)
unnamed: C51.2, U9.7 (DVDT)
unnamed: R76.1, R77.2, U9.4 (PGTH)
unnamed: R70.1, R92.2, U9.2 (nEN/OVLO)
unnamed: R71.2, U9.9 (IMON), U10.3 (IN1+)
unnamed: R72.2, R74.1, U10.2 (IN1-)
unnamed: R74.2, R79.1, U10.1 (OUT1)
unnamed: R73.2, R75.1, U10.6 (IN2-)
unnamed: R75.2, R80.1, U10.7 (OUT2)

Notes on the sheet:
${PRODUCT_NAME}
Overvoltage lockout: R90/R91/R92 1.07M with R51/R52/R70 100K on nEN/OVLO. Off above 14.0 V (13.4-14.7 V), back on below 12.75 V (12.2-13.4 V), so a tripped switch always recovers on the 12.03 V rail. PGTH dividers R59/R61/R76 390K over R60/R62/R77 51K: PG at 10.38 V (11.17 V worst case); 23.5 uA at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
R53 (DAQ) and R71 (EXT) set the U6/U9 current limits: ILIM = 6595 / R (1K = 6.6 A, up to 7.1 A with IMON gain tolerance). J6 and J5 carry each output on one 6.5 A contact: once the final loads are known, raise R53/R71 (1.2K or more) to keep ILIM at or below 6.5 A. This also rescales IAMPDAQ/IAMPEXT.
Denotes Layout instructions
SHEET NUMBER
MODULE:
${SCH_REVISION}
REVISION:
PRODUCT NAME:
DATE:
PCB NUMBER:
DAQ (U6) is deliberately different from SBC and EXT. U6 has an 11 V undervoltage lockout: R108/R49 turn it on at 11.1 V (10.6-11.9 V) and off at 10.1 V (9.7-10.9 V). That divider must hold EN/UVLO, so the enable goes through Q24: nENDAQ is active LOW. High or floating (POR, expander in reset or unp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
Load Switch and I-Sense
${CURRENT_DATE}
${BOARD_NUMBER}
${##}
Denotes text on the Identification layer on the PCB
${#}
Text
